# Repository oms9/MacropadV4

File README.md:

# MacropadV4

MacropadV4 is an ortholinear 40-key (5 rows, 8 columns) Macropad with 3 EC11 encoders. It's main purpose is volume control and to provide extra keys off of my main keyboard for use as a soundboard or to map to hotkeys, similar to a compact [Novation launchpad](https://us.novationmusic.com/products/launchpad-x). <br></br>

It is based on the [Rasbperry Pi Pico/W](https://www.raspberrypi.com/products/raspberry-pi-pico/) with individual RGB backlight support. It runs on [QMK](https://qmk.fm/), mainly compiled for use with [Vial](https://get.vial.today/). <br></br>

It communicates with the host using [MIDI](https://en.wikipedia.org/wiki/MIDI) signals to prevent games like League of Legends, VALORANT, Apex Legends and similar from intercepting the key presses from reaching control software.<br></br>

It is my first time designing a PCB as well as my first interaction with QMK!!<br></br>

KiCad PCB Design files (Schematic and PCB) as well as 3D CAD files (Shell with kickstand and keycaps) and the Vial configuration (as well as pre-compiled firmware) are all included, I ordered PCB fabrication from [JLC PCB](https://jlcpcb.com/), the 3D prints are mostly in PETG with the exception of the green shell.<br></br>

When it comes to control software, I wrote my own GUI application: [MIDI Controls V2](github repo coming soon!)

## [Images](https://imgur.com/a/Uc7NvE1):

---
## Bill of Materials:
 - 1 x [Raspberry Pi Pico or Pico W](https://www.raspberrypi.com/products/raspberry-pi-pico/)
 - 40 x [MX Style switches](https://www.amazon.com/gp/product/B0C289CZT7/)
 - 40 x [Kailh Hotswap sockets](https://www.amazon.com/gp/product/B0B4W9YMGM/) 
 - 40 x [1N4148W diodes](https://www.amazon.com/gp/product/B0BY6ZL9BH/) (SOD-123 footprint)
 - 40 x [WS2812B RGB LEDs](https://www.ebay.com/itm/266150587894?var=565982726008)
 - 4 x M4 x 8.1mm x 6.3mm [threaded inserts](https://www.amazon.com/gp/product/B0BFWC4Q9P/)
 - 2 x M4 x 12mm hex head screws
 - 2 x M4 x 7.5mm hex head screws

---

## Notes and Instructions:

#### ⚠️ For the PCB, please note that the WS2812B LEDs are rotated by 180° every other row! ⚠️
#### I recommend printing the shell with manual supports underneath the kickstand recess, keycaps are printed face down.

I recommend the following order when it comes to assembling the PCB:

 1. Refer to the image album.
 2. Pre tin the pads
 3. Solder the RGB LEDs, keep in mind that they rotate 180° every other row
    - Start with the top row and the LED's corner to the top left, second row it should be bottom right, alternate.
 5. Solder the 1N4148W diodes
 6. Solder the hot swap sockets
 7. Solder the Pico's pin headers ⚠️ long side at the bottom (Pico should be on the right).
 8. Place the Pico on the front side of the board (Pico should be on the left) and solder it to the headers.

After the assembly, you can just plug in the Pi Pico to your computer and copy the .uf2 file to the directory that shows up, this will essentially flash the Vial firmware to the Macropad and you are ready to go! You can use Vial (or the [web-app](https://vial.rocks/)) to customize the keys and lighting to your liking.

#### The encoder's push switches are wired to individual GPIO pins and GND, which is normal if you are using Micro/CircuitPython for the keyboard, but it is not directly supported by QMK. They still work however because I added extra columns in firmware to trick QMK into treating them as part of the key matrix. So this is a solved problem!

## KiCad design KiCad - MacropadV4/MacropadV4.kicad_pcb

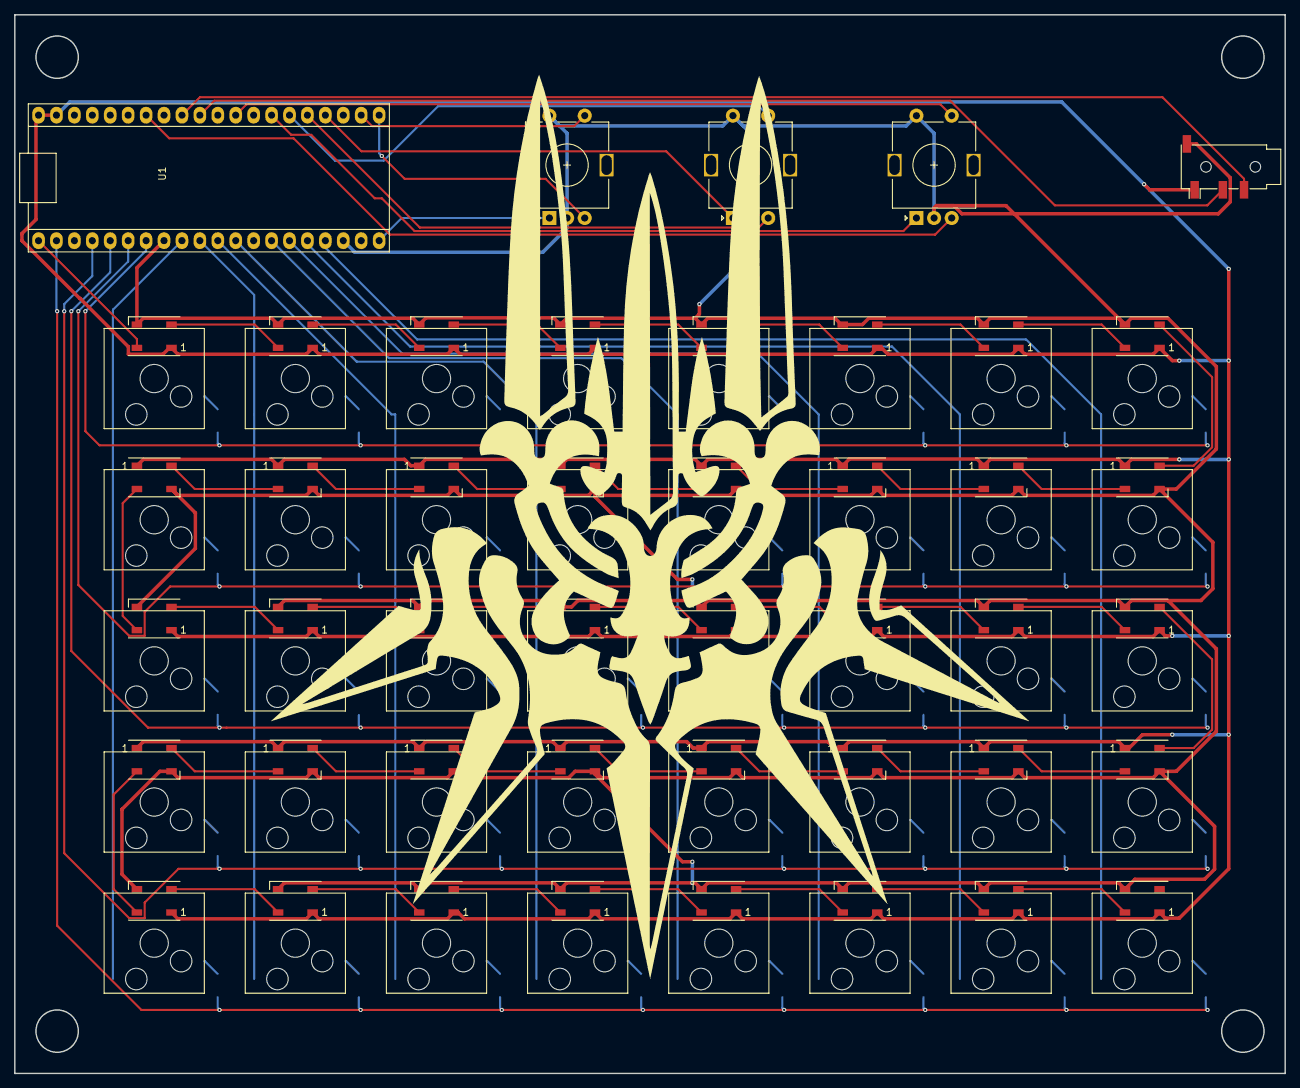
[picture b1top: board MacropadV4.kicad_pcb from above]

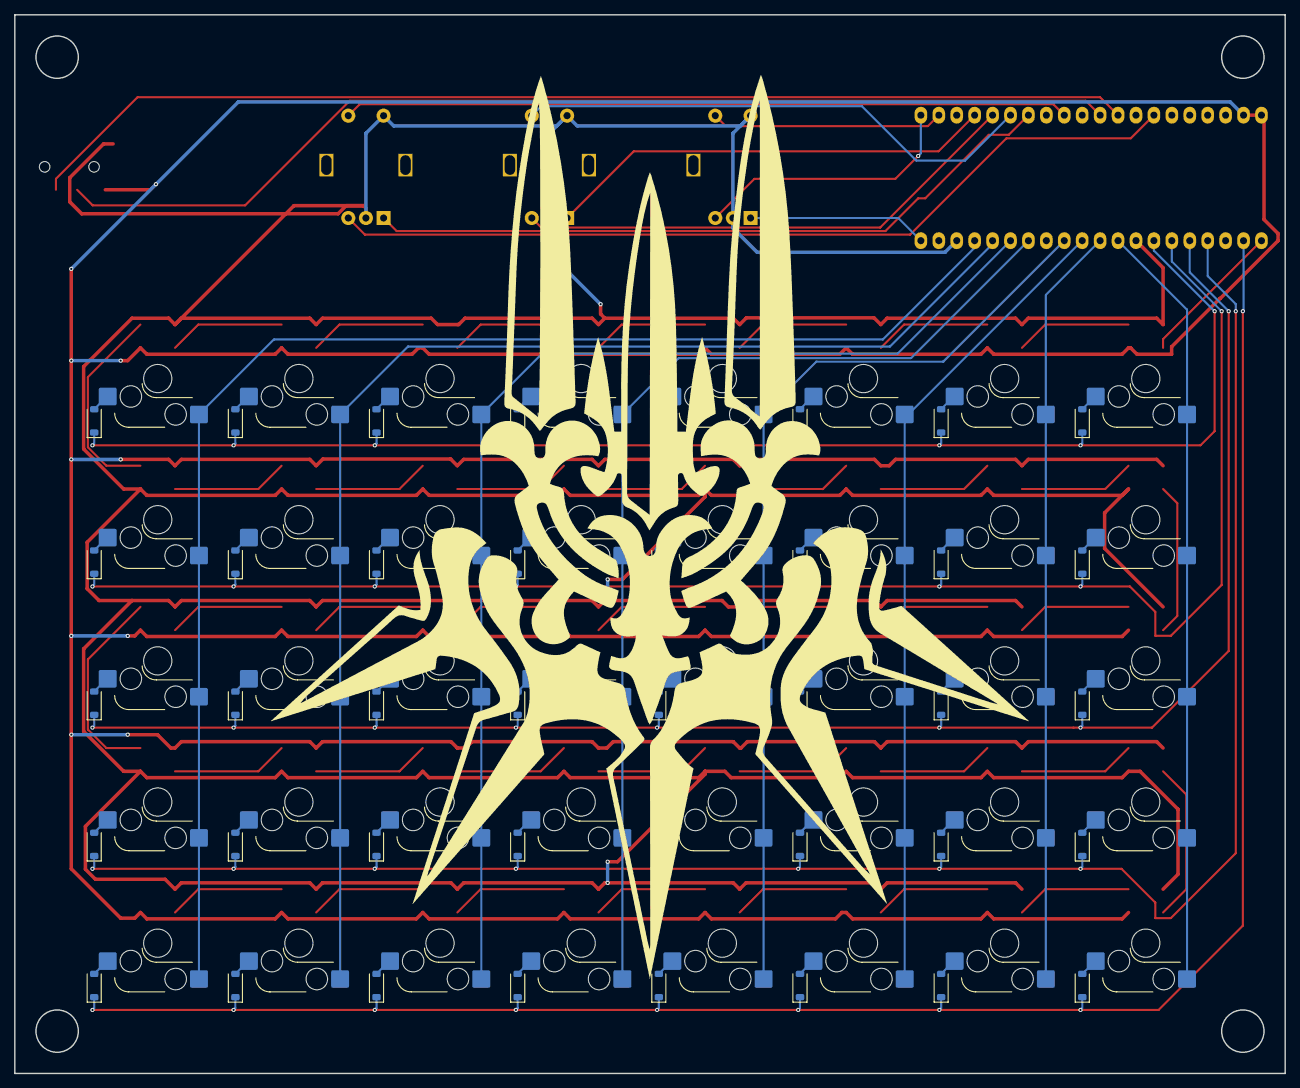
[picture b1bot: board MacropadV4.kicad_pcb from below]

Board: 2 copper layers, 180.0 x 150.0 mm, 125 parts (40 on the bottom side), 106 nets.

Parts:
D1, D2, D3, D4, D5, D6, D7, D8, D9, D10, D11, D12, D13, D14, D15, D16, D17, D18, D19, D20, D21, D22, D23, D24, D25, D26, D27, D28, D29, D30, D31, D32, D33, D34, D35, D36, D37, D38, D39, D40: 1N4148W; D_SOD-123
D41, D42, D43, D44, D45, D46, D47, D48, D49, D50, D51, D52, D53, D54, D55, D56, D57, D58, D59, D60, D61, D62, D63, D64, D65, D66, D67, D68, D69, D70, D71, D72, D73, D74, D75, D76, D77, D78, D79, D80: WS2812B; LED_WS2812B_PLCC4_5.0x5.0mm_P3.2mm
J1: AudioJack4; Jack_3.5mm_PJ320D_Horizontal
SW1, SW2, SW3, SW4, SW5, SW6, SW7, SW8, SW9, SW10, SW11, SW12, SW13, SW14, SW15, SW16, SW17, SW18, SW19, SW20, SW21, SW22, SW23, SW24, SW25, SW26, SW27, SW28, SW29, SW30, SW31, SW32, SW33, SW34, SW35, SW36, SW37, SW38, SW39, SW40: SW_Push; SW_Hotswap_Kailh_MX_1.00u_MINE
SW41, SW42, SW43: RotaryEncoder_Switch; RotaryEncoder_Alps_EC11E-Switch_Vertical_H20mm
U1: Pico_W_TestPads; raspberry_pi_pico_THT

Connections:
+ ENC1: SW41.A, U1.20 (GP15)
+ ENC2: SW42.A, U1.24 (GP18)
+ ENC3: SW43.A, U1.27 (GP21)
- ENC1: SW41.B, U1.21 (GP16)
- ENC2: SW42.B, U1.25 (GP19)
- ENC3: SW43.B, U1.34 (GP28/ADC2)
Col 1: SW1.2, SW2.2, SW3.2, SW4.2, SW5.2, U1.9 (GP6)
Col 2: SW6.2, SW7.2, SW8.2, SW9.2, SW10.2, U1.10 (GP7)
Col 3: SW11.2, SW12.2, SW13.2, SW14.2, SW15.2, U1.11 (GP8)
Col 4: SW16.2, SW17.2, SW18.2, SW19.2, SW20.2, U1.12 (GP9)
Col 5: SW21.2, SW22.2, SW23.2, SW24.2, SW25.2, U1.14 (GP10)
Col 6: SW26.2, SW27.2, SW28.2, SW29.2, SW30.2, U1.15 (GP11)
Col 7: SW31.2, SW32.2, SW33.2, SW34.2, SW35.2, U1.16 (GP12)
Col 8: SW36.2, SW37.2, SW38.2, SW39.2, SW40.2, U1.17 (GP13)
GND: D41.3 (VSS), D42.3 (VSS), D43.3 (VSS), D44.3 (VSS), D45.3 (VSS), D46.3 (VSS), D47.3 (VSS), D48.3 (VSS), D49.3 (VSS), D50.3 (VSS), D51.3 (VSS), D52.3 (VSS), D53.3 (VSS), D54.3 (VSS), D55.3 (VSS), D56.3 (VSS), D57.3 (VSS), D58.3 (VSS), D59.3 (VSS), D60.3 (VSS), D61.3 (VSS), D62.3 (VSS), D63.3 (VSS), D64.3 (VSS), D65.3 (VSS), D66.3 (VSS), D67.3 (VSS), D68.3 (VSS), D69.3 (VSS), D70.3 (VSS), D71.3 (VSS), D72.3 (VSS), D73.3 (VSS), D74.3 (VSS), D75.3 (VSS), D76.3 (VSS), D77.3 (VSS), D78.3 (VSS), D79.3 (VSS), D80.3 (VSS), J1.S, SW41.C, SW41.S2, SW42.C, SW42.S2, SW43.C, SW43.S2, U1.3 (GND), U1.8 (GND), U1.13 (GND), U1.18 (GND), U1.23 (GND), U1.28 (GND), U1.38 (GND)
I2C SCL: J1.R1, U1.31 (GP26/ADC0)
I2C SDA: J1.R2, U1.32 (GP27/ADC1)
unnamed: D1.2 (A), SW1.1
unnamed: D2.2 (A), SW2.1
unnamed: D3.2 (A), SW3.1
unnamed: D4.2 (A), SW4.1
unnamed: D5.2 (A), SW5.1
unnamed: D6.2 (A), SW6.1
unnamed: D7.2 (A), SW7.1
unnamed: D8.2 (A), SW8.1
unnamed: D9.2 (A), SW9.1
unnamed: D10.2 (A), SW10.1
unnamed: D11.2 (A), SW11.1
unnamed: D12.2 (A), SW12.1
unnamed: D13.2 (A), SW13.1
unnamed: D14.2 (A), SW14.1
unnamed: D15.2 (A), SW15.1
unnamed: D16.2 (A), SW16.1
unnamed: D17.2 (A), SW17.1
unnamed: D18.2 (A), SW18.1
unnamed: D19.2 (A), SW19.1
unnamed: D20.2 (A), SW20.1
unnamed: D21.2 (A), SW21.1
unnamed: D22.2 (A), SW22.1
unnamed: D23.2 (A), SW23.1
unnamed: D24.2 (A), SW24.1
unnamed: D25.2 (A), SW25.1
unnamed: D26.2 (A), SW26.1
unnamed: D27.2 (A), SW27.1
unnamed: D28.2 (A), SW28.1
unnamed: D29.2 (A), SW29.1
unnamed: D30.2 (A), SW30.1
unnamed: D31.2 (A), SW31.1
unnamed: D32.2 (A), SW32.1
unnamed: D33.2 (A), SW33.1
unnamed: D34.2 (A), SW34.1
unnamed: D35.2 (A), SW35.1
unnamed: D36.2 (A), SW36.1
unnamed: D37.2 (A), SW37.1
unnamed: D38.2 (A), SW38.1
unnamed: D39.2 (A), SW39.1
unnamed: D40.2 (A), SW40.1
unnamed: D41.2 (DOUT), D42.4 (DIN)
unnamed: D42.2 (DOUT), D43.4 (DIN)
unnamed: D43.2 (DOUT), D44.4 (DIN)
unnamed: D44.2 (DOUT), D45.4 (DIN)
unnamed: D45.2 (DOUT), D46.4 (DIN)
unnamed: D46.2 (DOUT), D47.4 (DIN)
unnamed: D47.2 (DOUT), D48.4 (DIN)
unnamed: D48.2 (DOUT), D49.4 (DIN)
unnamed: D49.2 (DOUT), D50.4 (DIN)
unnamed: D50.2 (DOUT), D51.4 (DIN)
unnamed: D51.2 (DOUT), D52.4 (DIN)
unnamed: D52.2 (DOUT), D53.4 (DIN)
unnamed: D53.2 (DOUT), D54.4 (DIN)
unnamed: D54.2 (DOUT), D55.4 (DIN)
unnamed: D55.2 (DOUT), D56.4 (DIN)
unnamed: D56.2 (DOUT), D57.4 (DIN)
unnamed: D57.2 (DOUT), D58.4 (DIN)
unnamed: D58.2 (DOUT), D59.4 (DIN)
unnamed: D59.2 (DOUT), D60.4 (DIN)
unnamed: D60.2 (DOUT), D61.4 (DIN)
unnamed: D61.2 (DOUT), D62.4 (DIN)
unnamed: D62.2 (DOUT), D63.4 (DIN)
unnamed: D63.2 (DOUT), D64.4 (DIN)
unnamed: D64.2 (DOUT), D65.4 (DIN)
unnamed: D65.2 (DOUT), D66.4 (DIN)
unnamed: D66.2 (DOUT), D67.4 (DIN)
unnamed: D67.2 (DOUT), D68.4 (DIN)
unnamed: D68.2 (DOUT), D69.4 (DIN)
unnamed: D69.2 (DOUT), D70.4 (DIN)
unnamed: D70.2 (DOUT), D71.4 (DIN)
unnamed: D71.2 (DOUT), D72.4 (DIN)
unnamed: D72.2 (DOUT), D73.4 (DIN)
unnamed: D73.2 (DOUT), D74.4 (DIN)
unnamed: D74.2 (DOUT), D75.4 (DIN)
unnamed: D75.2 (DOUT), D76.4 (DIN)
unnamed: D76.2 (DOUT), D77.4 (DIN)
unnamed: D77.2 (DOUT), D78.4 (DIN)
unnamed: D78.2 (DOUT), D79.4 (DIN)
unnamed: D79.2 (DOUT), D80.4 (DIN)
RGB DIN: D41.4 (DIN), U1.1 (GP0)
Row 1: D1.1 (K), D6.1 (K), D11.1 (K), D16.1 (K), D21.1 (K), D26.1 (K), D31.1 (K), D36.1 (K), U1.7 (GP5)
Row 2: D2.1 (K), D7.1 (K), D12.1 (K), D17.1 (K), D22.1 (K), D27.1 (K), D32.1 (K), D37.1 (K), U1.6 (GP4)
Row 3: D3.1 (K), D8.1 (K), D13.1 (K), D18.1 (K), D23.1 (K), D28.1 (K), D33.1 (K), D38.1 (K), U1.5 (GP3)
Row 4: D4.1 (K), D9.1 (K), D14.1 (K), D19.1 (K), D24.1 (K), D29.1 (K), D34.1 (K), D39.1 (K), U1.4 (GP2)
Row 5: D5.1 (K), D10.1 (K), D15.1 (K), D20.1 (K), D25.1 (K), D30.1 (K), D35.1 (K), D40.1 (K), U1.2 (GP1)
S ENC1: SW41.S1, U1.22 (GP17)
S ENC2: SW42.S1, U1.26 (GP20)
S ENC3: SW43.S1, U1.29 (GP22)
VSYS/5V: D41.1 (VDD), D42.1 (VDD), D43.1 (VDD), D44.1 (VDD), D45.1 (VDD), D46.1 (VDD), D47.1 (VDD), D48.1 (VDD), D49.1 (VDD), D50.1 (VDD), D51.1 (VDD), D52.1 (VDD), D53.1 (VDD), D54.1 (VDD), D55.1 (VDD), D56.1 (VDD), D57.1 (VDD), D58.1 (VDD), D59.1 (VDD), D60.1 (VDD), D61.1 (VDD), D62.1 (VDD), D63.1 (VDD), D64.1 (VDD), D65.1 (VDD), D66.1 (VDD), D67.1 (VDD), D68.1 (VDD), D69.1 (VDD), D70.1 (VDD), D71.1 (VDD), D72.1 (VDD), D73.1 (VDD), D74.1 (VDD), D75.1 (VDD), D76.1 (VDD), D77.1 (VDD), D78.1 (VDD), D79.1 (VDD), D80.1 (VDD), J1.T, U1.39 (VSYS), U1.40 (VBUS)

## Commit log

2024-06-29 First commit.
    Adding all the files.
2024-06-29 Update README.md
    Updating README.
2024-06-29 Update README.md
    clarification about MIDI Controls V2
2025-02-17 Update README.md
    Fixed image links.
2025-02-17 Update README.md
    Fix Imgur embeds.
